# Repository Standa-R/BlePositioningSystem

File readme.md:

# BLE positioning system

The project includes a short description of source code for Anchors and Tags. PCB design files are also included.

If the use of this source code for Anchors and Tags or PCB design leading to a scientific publication, please, cite our work:

```
@article{Polak_Sensors_2021,
     doi = {10.3390/s21134605},
     url = {https://doi.org/10.3390/s21134605},
     year = {2021},
     month = {July},
     publisher = {MDPI},
     volume = {21},
     number = {13},
     pages = {1--25},
     author = {Ladislav Polak and Stanislav Rozum and Martin Slanina and Tomas Bravenec and Tomas Fryza and Aggelos Pikrakis},
     title = {Received Signal Strength Fingerprinting-Based Indoor Location Estimation Employing Machine Learning},
     journal = {Sensors}
}
```

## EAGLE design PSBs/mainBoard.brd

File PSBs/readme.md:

# PCB design

This folder contains Anchor's PCB source files from Autodesk Eagle. The mainBoard includes board-to-board connectors for extension boards. There are two extension boards, namely BLEModule and ZigBeeModule. Both are directly put into the schematic of mainBoard.

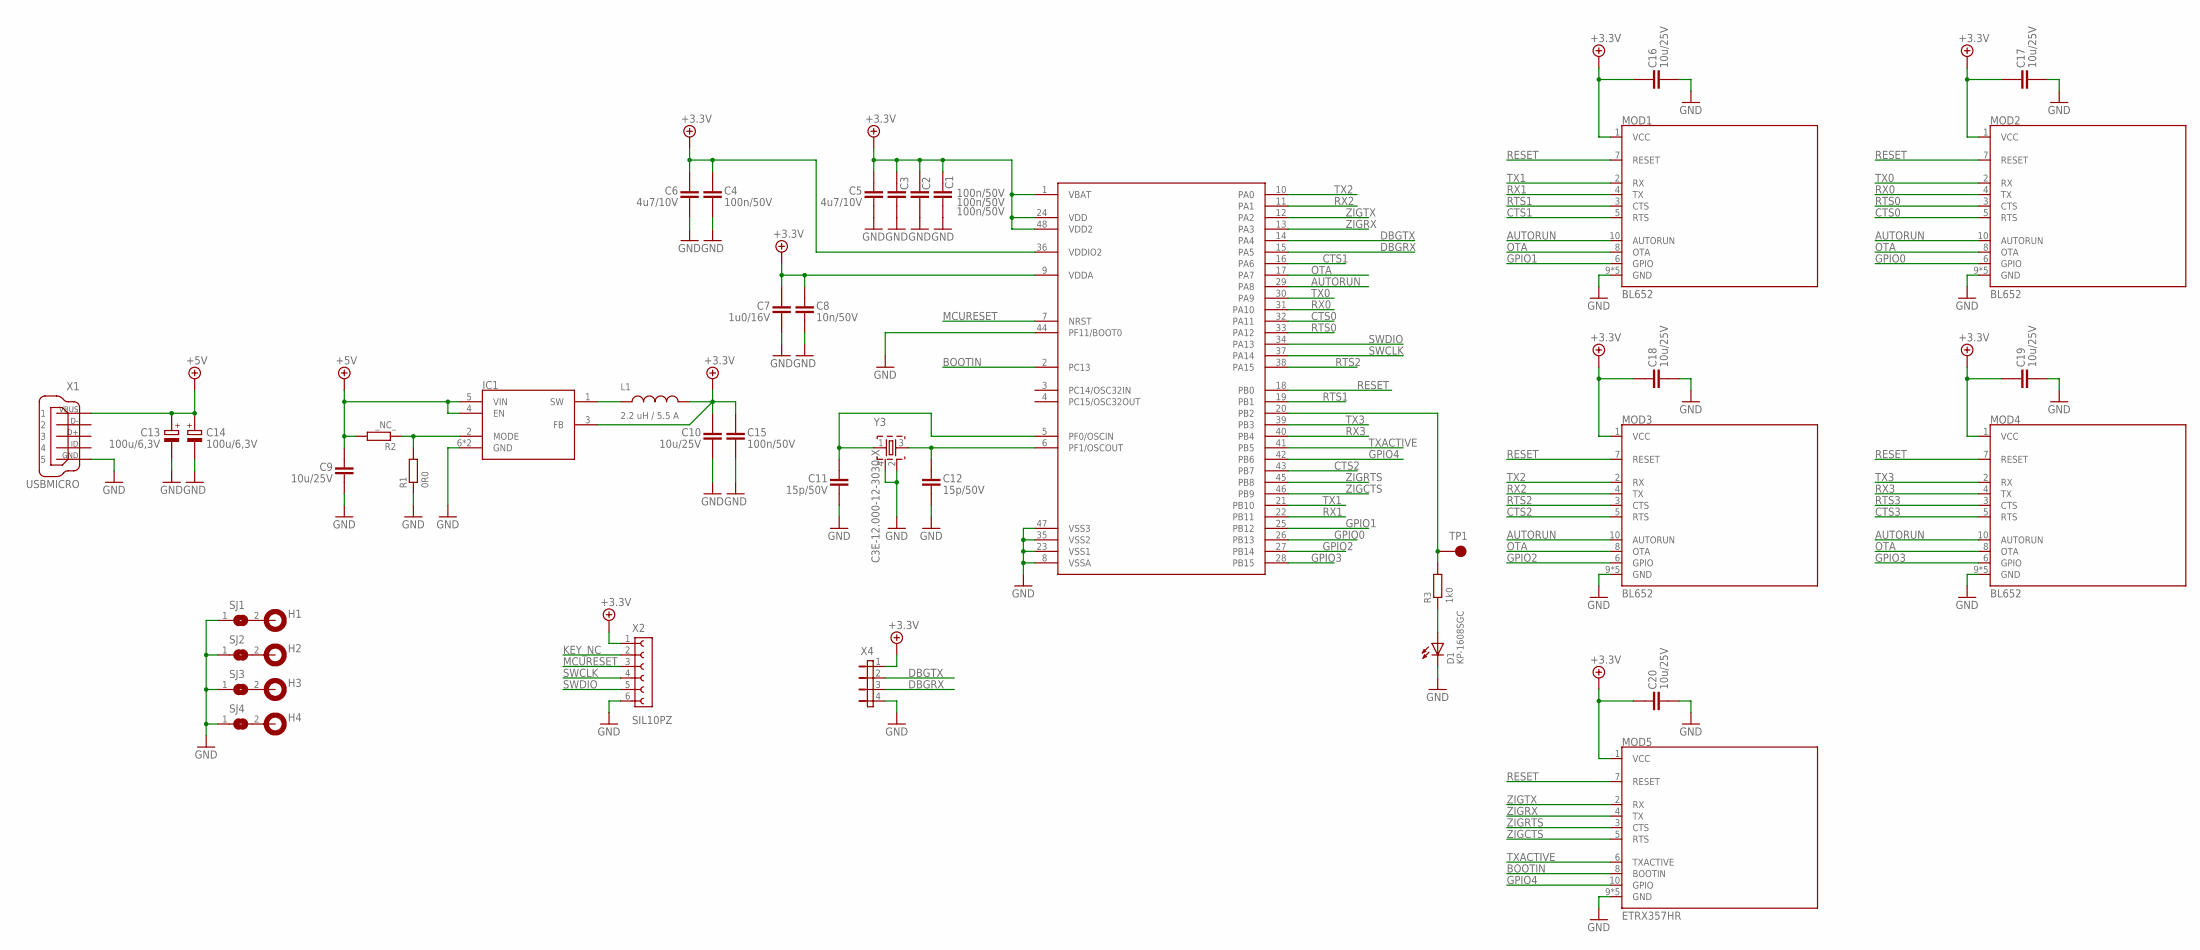
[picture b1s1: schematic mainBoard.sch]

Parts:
C1, C2, C3, C4, C15: 100N/50V,X7R,+/-10%_0603R; C0603R
C5, C6: 4U7/10V,X5R,+/-10%_0603R; C0603R
C7: 1U0/16V,X5R,+/-10%_0603R; C0603R
C8: 10N/50V,X7R,+/-10%_0603R; C0603R
C9, C10, C16, C17, C18, C19, C20: 10U/25V,X5R,+/-10%_0805R; C0805R
C11, C12: 15P/50V,COG/NPO,+/-5%_0603R; C0603R
C13, C14: 100U; CT6032
D1: KP-1608SGC; 0603
H1, H2, H3, H4: MOUNT-PAD-ROUND4.3; 4.3-PAD
IC0: STM32F091CCT; LQFP48
IC1: TPS62291
L1: 2U2_IHLP2020; 5.49X2X5.18MM
MOD1, MOD2, MOD3, MOD4: BLEMODULE; BLEMOD
MOD5: ZIGBEE; ZIGBEEMOD
R1: 0R0/0.1W,THICK_FILM,1%_0603R; R0603R
R2: _NC_/0.1W,THICK_FILM,1%_0603R; R0603R
R3: 1K0/0.1W,THICK_FILM,1%_0603R; R0603R
SJ1, SJ2, SJ3, SJ4: SJ_1-SMALL; SJ-SMALL
TP1: TEST-PAD_3.5X2-SMD; 3.5X2_SMD
X1: USBMICRO
X2: SOCKET_HADER-1X6; 1X06
X4: PIN_HEADER-1X4; 1X04
Y3: C3E-12.000-12-3030-X; 3.4X2.7X0.75

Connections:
+3.3V: C1.2, C2.2, C3.2, C4.2, C5.2, C6.2, C7.2, C8.2, C10.2, C15.2, C16.2, C17.2, C18.2, C19.2, C20.2, IC0.1 (VBAT), IC0.9 (VDDA), IC0.24 (VDD), IC0.36 (VDDIO2), IC0.48 (VDD2), IC1.3 (FB), L1.P$2 (2), MOD1.1 (VCC), MOD2.1 (VCC), MOD3.1 (VCC), MOD4.1 (VCC), MOD5.1 (VCC), X2.1, X4.1
+5V: C9.2, C13.+, C14.+, IC1.4 (EN), IC1.5 (VIN), R2.2, X1.1
AUTORUN: IC0.29 (PA8), MOD1.10 (AUTORUN), MOD2.10 (AUTORUN), MOD3.10 (AUTORUN), MOD4.10 (AUTORUN)
BOOTIN: IC0.2 (PC13), MOD5.8 (BOOTIN)
CTS0: IC0.32 (PA11), MOD2.5 (RTS)
CTS1: IC0.16 (PA6), MOD1.5 (RTS)
CTS2: IC0.43 (PB7), MOD3.5 (RTS)
CTS3: MOD4.5 (RTS)
DBGRX: IC0.15 (PA5), X4.3
DBGTX: IC0.14 (PA4), X4.2
GND: C1.1, C2.1, C3.1, C4.1, C5.1, C6.1, C7.1, C8.1, C9.1, C10.1, C11.1, C12.1, C13.-, C14.-, C15.1, C16.1, C17.1, C18.1, C19.1, C20.1, D1.2 (C), IC0.8 (VSSA), IC0.23 (VSS1), IC0.35 (VSS2), IC0.44 (PF11/BOOT0), IC0.47 (VSS3), IC1.6 (GND), IC1.EXP (GND), MOD1.9 (GND), MOD1.A1 (GND), MOD1.A2 (GND), MOD1.B1 (GND), MOD1.B2 (GND), MOD2.9 (GND), MOD2.A1 (GND), MOD2.A2 (GND), MOD2.B1 (GND), MOD2.B2 (GND), MOD3.9 (GND), MOD3.A1 (GND), MOD3.A2 (GND), MOD3.B1 (GND), MOD3.B2 (GND), MOD4.9 (GND), MOD4.A1 (GND), MOD4.A2 (GND), MOD4.B1 (GND), MOD4.B2 (GND), MOD5.9 (GND), MOD5.A1 (GND), MOD5.A2 (GND), MOD5.B1 (GND), MOD5.B2 (GND), R1.1, SJ1.1, SJ2.1, SJ3.1, SJ4.1, X1.5, X1.H1 (5), X1.H2 (5), X2.6, X4.4, Y3.2, Y3.4
GPIO0: IC0.26 (PB13), MOD2.6 (GPIO)
GPIO1: IC0.25 (PB12), MOD1.6 (GPIO)
GPIO2: IC0.27 (PB14), MOD3.6 (GPIO)
GPIO3: IC0.28 (PB15), MOD4.6 (GPIO)
GPIO4: IC0.42 (PB6), MOD5.10 (GPIO)
KEY_NC: X2.2
MCURESET: IC0.7 (NRST), X2.3
unnamed: IC1.1 (SW), L1.P$1 (1)
unnamed: D1.1 (A), R3.1
unnamed: IC0.20 (PB2), R3.2, TP1.TP
unnamed: IC1.2 (MODE), R1.2, R2.1
unnamed: H1.1, SJ1.2
unnamed: H2.1, SJ2.2
unnamed: H3.1, SJ3.2
unnamed: H4.1, SJ4.2
unnamed: C11.2, IC0.5 (PF0/OSCIN), Y3.1
unnamed: C12.2, IC0.6 (PF1/OSCOUT), Y3.3
OTA: IC0.17 (PA7), MOD1.8 (OTA), MOD2.8 (OTA), MOD3.8 (OTA), MOD4.8 (OTA)
RESET: IC0.18 (PB0), MOD1.7 (RESET), MOD2.7 (RESET), MOD3.7 (RESET), MOD4.7 (RESET), MOD5.7 (RESET)
RTS0: IC0.33 (PA12), MOD2.3 (CTS)
RTS1: IC0.19 (PB1), MOD1.3 (CTS)
RTS2: IC0.38 (PA15), MOD3.3 (CTS)
RTS3: MOD4.3 (CTS)
RX0: IC0.31 (PA10), MOD2.4 (TX)
RX1: IC0.22 (PB11), MOD1.4 (TX)
RX2: IC0.11 (PA1), MOD3.4 (TX)
RX3: IC0.40 (PB4), MOD4.4 (TX)
SWCLK: IC0.37 (PA14), X2.4
SWDIO: IC0.34 (PA13), X2.5
TX0: IC0.30 (PA9), MOD2.2 (RX)
TX1: IC0.21 (PB10), MOD1.2 (RX)
TX2: IC0.10 (PA0), MOD3.2 (RX)
TX3: IC0.39 (PB3), MOD4.2 (RX)
TXACTIVE: IC0.41 (PB5), MOD5.6 (TXACTIVE)
ZIGCTS: IC0.46 (PB9), MOD5.5 (RTS)
ZIGRTS: IC0.45 (PB8), MOD5.3 (CTS)
ZIGRX: IC0.13 (PA3), MOD5.4 (TX)
ZIGTX: IC0.12 (PA2), MOD5.2 (RX)

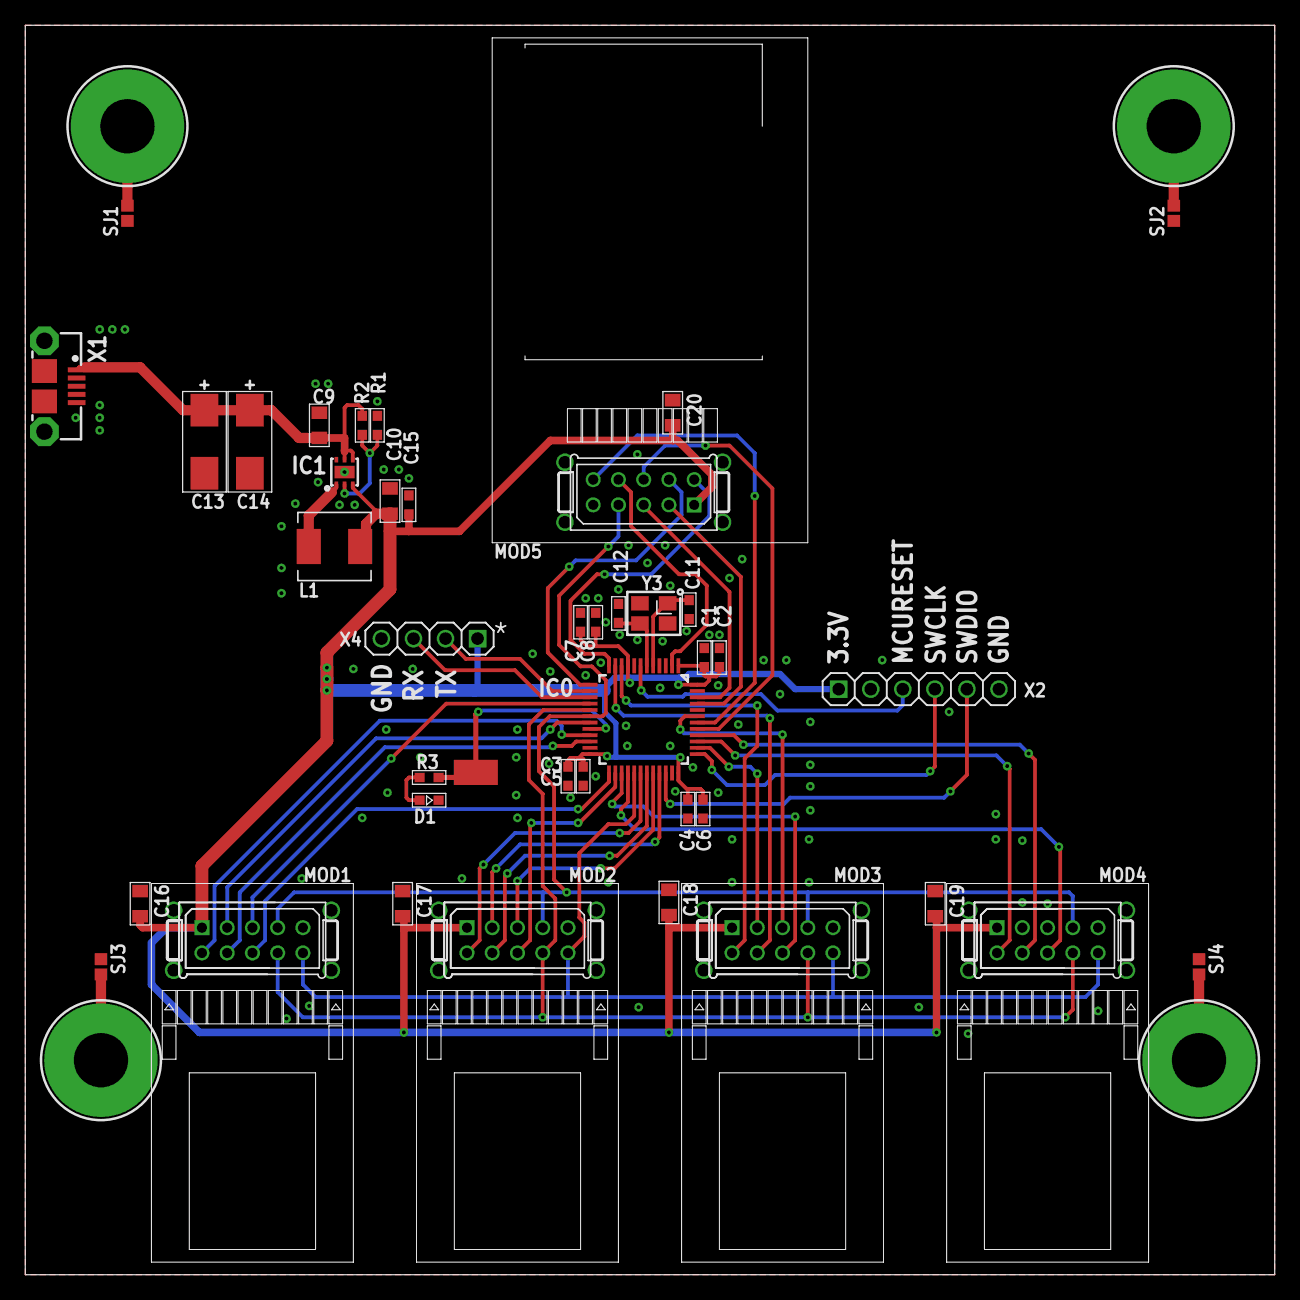
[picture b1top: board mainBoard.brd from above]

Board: 4 copper layers, 99.0 x 99.0 mm, 45 parts (0 on the bottom side), 46 nets.

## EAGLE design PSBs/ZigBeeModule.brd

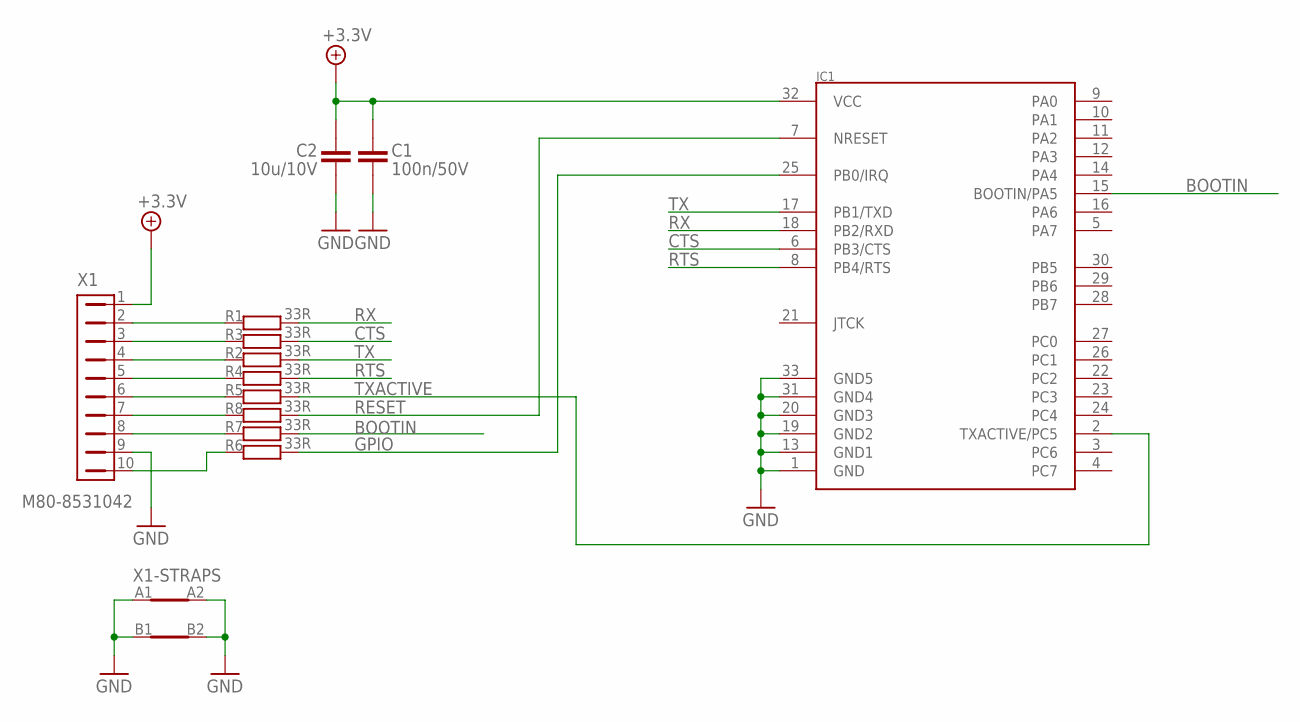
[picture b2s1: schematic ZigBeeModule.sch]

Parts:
C1: 100N/50V,X7R,+/-10%_0603R; C0603R
C2: 10U/10V,X5R,+/-20%_0603R; C0603R
IC1: ETRX357; ETRX3
R1, R2, R3, R4, R5, R6, R7, R8: 33R/0.1W,THICK_FILM,1%_0603R; R0603R
X1: M80-8531042; M80-85310-W_STRAPS

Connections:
+3.3V: C1.2, C2.2, IC1.32 (VCC), X1.1
BOOTIN: IC1.15 (BOOTIN/PA5), R7.2
CTS: IC1.6 (PB3/CTS), R3.2
GND: C1.1, C2.1, IC1.1 (GND), IC1.13 (GND1), IC1.19 (GND2), IC1.20 (GND3), IC1.31 (GND4), IC1.33 (GND5), X1.9, X1.A1, X1.A2, X1.B1, X1.B2
GPIO: IC1.25 (PB0/IRQ), R6.2
unnamed: R6.1, X1.10
unnamed: R1.1, X1.2
unnamed: R3.1, X1.3
unnamed: R2.1, X1.4
unnamed: R4.1, X1.5
unnamed: R5.1, X1.6
unnamed: R7.1, X1.8
unnamed: R8.1, X1.7
RESET: IC1.7 (NRESET), R8.2
RTS: IC1.8 (PB4/RTS), R4.2
RX: IC1.18 (PB2/RXD), R1.2
TX: IC1.17 (PB1/TXD), R2.2
TXACTIVE: IC1.2 (TXACTIVE/PC5), R5.2

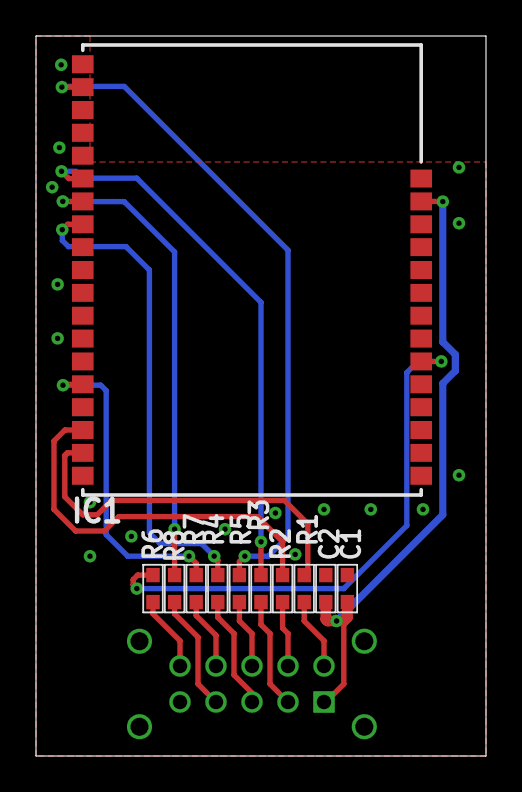
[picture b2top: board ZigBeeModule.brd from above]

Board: 4 copper layers, 25.0 x 40.0 mm, 12 parts (1 on the bottom side), 18 nets.

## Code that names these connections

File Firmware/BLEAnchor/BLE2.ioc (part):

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Mcu.Name=STM32F091C(B-C)Tx
Mcu.Package=LQFP48
Mcu.UserName=STM32F091CCTx
PA0.Mode=Asynchronous
PA0.Signal=USART4_TX
PA1.Mode=Asynchronous
PA1.Signal=USART4_RX
PA10.Mode=Asynchronous
PA10.Signal=USART1_RX
PA11.Mode=CTS_Only
PA11.Signal=USART1_CTS
PA13.Mode=Serial_Wire
PA13.Signal=SYS_SWDIO
PA14.Mode=Serial_Wire
PA14.Signal=SYS_SWCLK
PA2.Mode=Asynchronous
PA2.Signal=USART2_TX
PA3.Mode=Asynchronous
PA3.Signal=USART2_RX
PA4.Mode=Asynchronous
PA4.Signal=USART6_TX
PA5.Mode=Asynchronous
PA5.Signal=USART6_RX
PA6.Mode=CTS_Only
PA6.Signal=USART3_CTS
PA7.GPIOParameters=GPIO_Label
PA7.GPIO_Label=OTA
PA7.Signal=GPIO_Output
PA8.GPIOParameters=GPIO_Label
PA8.GPIO_Label=Autorun
PA8.Signal=GPIO_Output
PA9.Mode=Asynchronous
PA9.Signal=USART1_TX
PB0.GPIOParameters=GPIO_Label
PB0.GPIO_Label=Reset
PB0.Signal=GPIO_Output
PB10.Mode=Asynchronous
PB10.Signal=USART3_TX
PB11.Mode=Asynchronous
PB11.Signal=USART3_RX
PB12.GPIOParameters=GPIO_Label
PB12.GPIO_Label=GPIO3
PB12.Signal=GPIO_Input
PB13.GPIOParameters=GPIO_Label
PB13.GPIO_Label=GPIO2
PB13.Signal=GPIO_Input
PB14.GPIOParameters=GPIO_Label
PB14.GPIO_Label=GPIO1
PB14.Signal=GPIO_Input
PB15.GPIOParameters=GPIO_Label
PB15.GPIO_Label=GPIO0
PB15.Signal=GPIO_Input
PB2.GPIOParameters=GPIO_Label
PB2.GPIO_Label=LED
PB2.Signal=GPIO_Output
PB3.Mode=Asynchronous
PB3.Signal=USART5_TX
PB4.Mode=Asynchronous
PB4.Signal=USART5_RX
PB5.GPIOParameters=GPIO_Label
PB5.GPIO_Label=TXACTIVE
PB5.Signal=GPIO_Input
PB6.GPIOParameters=GPIO_Label
PB6.GPIO_Label=GPIO4
PB6.Signal=GPIO_Input
PB7.Mode=CTS_Only
PB7.Signal=USART4_CTS
PB8.GPIOParameters=GPIO_Label
PB8.GPIO_Label=ZIGRTS
PB8.Signal=GPIO_Output
PB9.GPIOParameters=GPIO_Label
PB9.GPIO_Label=ZIGCTS
PB9.Signal=GPXTI9
PC13.GPIOParameters=GPIO_Label
PC13.GPIO_Label=BOOTIN
PC13.Signal=GPIO_Output
PF0-OSC_IN.Mode=HSE-External-Oscillator
PF0-OSC_IN.Signal=RCC_OSC_IN
PF1-OSC_OUT.Mode=HSE-External-Oscillator
PF1-OSC_OUT.Signal=RCC_OSC_OUT
PF11BOOT0.Signal=GPIO_Input
RCC.HSE_VALUE=12000000
RCC.SYSCLKFreq_VALUE=24000000
RCC.SYSCLKSource=RCC_SYSCLKSOURCE_PLLCLK
board=custom

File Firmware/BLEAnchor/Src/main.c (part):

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  


  HAL_GPIO_WritePin(BOOTIN_GPIO_Port, BOOTIN_Pin, GPIO_PIN_SET);    //do not boot in bootloader mode (RTX357)

  HAL_Delay(200);

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}

/**
  * @brief GPIO Initialization Function
  * @param None
  * @retval None
  */
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{
  GPIO_InitTypeDef GPIO_InitStruct = {0};

  /* GPIO Ports Clock Enable */
  __HAL_RCC_GPIOC_CLK_ENABLE();
  __HAL_RCC_GPIOF_CLK_ENABLE();
  __HAL_RCC_GPIOA_CLK_ENABLE();
  __HAL_RCC_GPIOB_CLK_ENABLE();

  /*Configure GPIO pin Output Level */
  HAL_GPIO_WritePin(BOOTIN_GPIO_Port, BOOTIN_Pin, GPIO_PIN_RESET);

  /*Configure GPIO pin Output Level */
  HAL_GPIO_WritePin(GPIOA, OTA_Pin|Autorun_Pin, GPIO_PIN_RESET);

  /*Configure GPIO pin Output Level */
  HAL_GPIO_WritePin(GPIOB, Reset_Pin|LED_Pin|ZIGRTS_Pin, GPIO_PIN_RESET);

  /*Configure GPIO pin : BOOTIN_Pin */
  GPIO_InitStruct.Pin = BOOTIN_Pin;
  GPIO_InitStruct.Mode = GPIO_MODE_OUTPUT_PP;
  GPIO_InitStruct.Pull = GPIO_NOPULL;
  GPIO_InitStruct.Speed = GPIO_SPEED_FREQ_LOW;
  HAL_GPIO_Init(BOOTIN_GPIO_Port, &GPIO_InitStruct);

  /*Configure GPIO pins : PC14 PC15 */
  GPIO_InitStruct.Pin = GPIO_PIN_14|GPIO_PIN_15;
  GPIO_InitStruct.Mode = GPIO_MODE_ANALOG;
  GPIO_InitStruct.Pull = GPIO_NOPULL;
  HAL_GPIO_Init(GPIOC, &GPIO_InitStruct);

  /*Configure GPIO pins : OTA_Pin Autorun_Pin */
  GPIO_InitStruct.Pin = OTA_Pin|Autorun_Pin;
  GPIO_InitStruct.Mode = GPIO_MODE_OUTPUT_PP;
  GPIO_InitStruct.Pull = GPIO_NOPULL;
  GPIO_InitStruct.Speed = GPIO_SPEED_FREQ_LOW;
  HAL_GPIO_Init(GPIOA, &GPIO_InitStruct);

  /*Configure GPIO pins : Reset_Pin LED_Pin ZIGRTS_Pin */
  GPIO_InitStruct.Pin = Reset_Pin|LED_Pin|ZIGRTS_Pin;
  GPIO_InitStruct.Mode = GPIO_MODE_OUTPUT_PP;
  GPIO_InitStruct.Pull = GPIO_NOPULL;
  GPIO_InitStruct.Speed = GPIO_SPEED_FREQ_LOW;
  HAL_GPIO_Init(GPIOB, &GPIO_InitStruct);

  /*Configure GPIO pin : PB1 */
  GPIO_InitStruct.Pin = GPIO_PIN_1;
  GPIO_InitStruct.Mode = GPIO_MODE_ANALOG;
  GPIO_InitStruct.Pull = GPIO_NOPULL;
  HAL_GPIO_Init(GPIOB, &GPIO_InitStruct);

  /*Configure GPIO pins : GPIO3_Pin GPIO2_Pin GPIO1_Pin GPIO0_Pin 
                           TXACTIVE_Pin GPIO4_Pin */
  GPIO_InitStruct.Pin = GPIO3_Pin|GPIO2_Pin|GPIO1_Pin|GPIO0_Pin 
                          |TXACTIVE_Pin|GPIO4_Pin;
  GPIO_InitStruct.Mode = GPIO_MODE_INPUT;
  GPIO_InitStruct.Pull = GPIO_NOPULL;
  HAL_GPIO_Init(GPIOB, &GPIO_InitStruct);

  /*Configure GPIO pins : PA12 PA15 */
  GPIO_InitStruct.Pin = GPIO_PIN_12|GPIO_PIN_15;
  GPIO_InitStruct.Mode = GPIO_MODE_ANALOG;
  GPIO_InitStruct.Pull = GPIO_NOPULL;
  HAL_GPIO_Init(GPIOA, &GPIO_InitStruct);

  /*Configure GPIO pin : PF11 */
  GPIO_InitStruct.Pin = GPIO_PIN_11;
  GPIO_InitStruct.Mode = GPIO_MODE_INPUT;
  GPIO_InitStruct.Pull = GPIO_NOPULL;
  HAL_GPIO_Init(GPIOF, &GPIO_InitStruct);

  /*Configure GPIO pin : ZIGCTS_Pin */
  GPIO_InitStruct.Pin = ZIGCTS_Pin;
  GPIO_InitStruct.Mode = GPIO_MODE_IT_RISING;
  GPIO_InitStruct.Pull = GPIO_NOPULL;
  HAL_GPIO_Init(ZIGCTS_GPIO_Port, &GPIO_InitStruct);

}

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
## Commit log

2021-06-11 added software folder, the software runs on PC and logs messages from Raspberry Pi B+
2021-06-16 Added licence file
2021-07-21 Update readme.md
    added citation
2021-07-21 Update readme.md
    citation put into source code block
2021-07-21 Update readme.md
    added curly brackets around year value

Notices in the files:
Firmware/BLEAnchor/Src/main.c:
COPYRIGHT(c) 2018 STMicroelectronics
(C) COPYRIGHT STMicroelectronics *****END OF FILE
